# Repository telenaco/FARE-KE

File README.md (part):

# FARE-KE: Framework for Affordable, Reliable Kinesthetic Evaluation

## Overview

<p align="center"><span style="font-size: smaller;"><em>Figure 1: Exploded isometric view of the 6- and 3-axis load cell array assembly, showing the modular sensor housing units.</em></span></p>

FARE-KE is a comprehensive, standardized framework developed to address the growing need for accessible characterization methods for kinesthetic haptic devices. Born out of the challenges faced during the COVID-19 pandemic when laboratory access was limited, this framework provides researchers with the tools and methodologies to conduct precise haptic device evaluation using affordable components and open-source technologies.

The framework emerged from research on haptic device design and was refined through applications in three distinct case studies (VR Recoil, ProxyTouch, and HapticWhirl). FARE-KE aims to democratize haptic research by making characterization methods and tools accessible to researchers of all experience levels.

## Repository Structure

```
FARE-KE
├── Board_Evaluation
│   ├── ADC_Performance            # ADC testing and benchmarking studies
│   │   ├── adc_excitation_voltage_analysis  # Comparison of voltage stability
│   │   ├── adc_noise_variation_analysis     # Noise analysis at different OSR settings
│   │   └── adc_sampling_rate_analysis       # Evaluation of sampling performance
│   ├── Calibration_Methods        # Calibration methodologies for different load cells
│   │   ├── six_axis_calibration            # Matrix-based calibration approaches
│   │   └── three_axis_calibration          # Calibration for 3-axis sensors
│   └── Load_Cell_Comparison       # Comparative studies of load cell performance
│       ├── beam_load_cell_calibration      # Linear vs polynomial calibration
│       ├── beam_load_cell_comparison       # Temperature and drift analysis
│       └── hx711_vs_mcp3564_comparison     # Comparison of ADC performance
├── Haptic_Device_Testing
│   ├── Ramp_Response              # Implementation of ramp response analysis
│   │   ├── rampResponseAnalysis.py        # Analysis script for ramp data
│   │   └── rampResponseTelemetry.cpp      # Arduino code for ramp testing
│   └── Step_Response              # Implementation of step response analysis
│       ├── StepResponseAnalysis.py        # Analysis script for step data
│       └── stepResponseTelemetry.cpp      # Arduino code for step testing
├── MCP356x_Arduino_Library        # Core software components of FARE-KE
│   ├── lib/mcp356x                # Library for MCP356x ADCs
│   │   ├── examples               # Example implementations
│   │   │   ├── Basic              # Fundamental operations (reading, sampling)
│   │   │   ├── Calibration        # Calibration examples for different scenarios
│   │   │   ├── Comparison         # Comparison with other ADC technologies
│   │   │   ├── Filtering          # Signal filtering implementations
│   │   │   ├── LoadCells          # Multi-axis load cell configurations
│   │   │   └── Telemetry          # Data visualization and transmission
│   │   └── src                    # Core library source files
│   │       ├── MCP356x.cpp/h              # Base ADC interface
│   │       ├── MCP356x3axis.cpp/h         # 3-axis load cell support
│   │       ├── MCP356x6axis.cpp/h         # 6-axis force/torque plate
│   │       └── MCP356xScale.cpp/h         # Multi-load cell management
│   └── src                        # Main application code
├── MCP356x_DAQ_PCB_Board          # Hardware design for data acquisition
│   └── ffpcbBoard                 # Custom PCB for 12-channel data acquisition
│       ├── manufacturingPCB               # Gerber files for fabrication
│       └── PCB design files               # Schematics and BOM information
└── STL files and 3D models        # Physical components for framework implementation
    ├── 3-axis load cell STLs             # 3D printable parts for custom 3-axis sensors
    ├── 6-axis force plate STLs           # Components for force/torque plate assembly
    └── testbed designs                   # Mounting systems for various device types
```

## The FARE-KE Framework Architecture

FARE-KE consists of four integrated components to provide comprehensive haptic device characterization:

### 1. Hardware Framework

<p align="center"><span style="font-size: smaller;"><em>Figure 2: Complete 6-axis force/torque plate with ADC board and wiring, showing the integrated system.</em></span></p>

**Key Components:**
- **Load Cells**: Single-axis beam load cells, custom 3-axis, and 6-axis configurations
- **Data Acquisition System**: Custom PCB design integrating 3 x MCP3564 ADCs for 12-channel capture
- **Testbeds**: Modular aluminum designs for mounting kinesthetic devices and sensors

**Testbed Designs:**
The framework recommends using extruded aluminum (40×40mm) for testbed construction due to:
- Standardization and wide availability
- Excellent structural rigidity (minimal vibrations)
- Abundant accessories for mounting and adaptation
- Easy reconfiguration for different device sizes

The testbeds must be designed to emulate the device's operational context and accommodate the same quantity and configuration of actuators as the final prototype to ensure representative data capture.

The framework supports five types of kinesthetic feedback modalities:

1. **Direct Single-Axis Force**: For devices applying linear force directly to the user
2. **Single-Axis Impact**: For devices generating sudden bursts of energy
3. **In-line Forces**: For cable-driven exoskeletons and similar devices
4. **Rotational Joint Torque**: For devices generating torque around a pivot point
5. **Multi-axis Force/Torque**: For complex haptic controllers with multiple degrees of freedom

### 2. Data Acquisition Framework

**Components:**
- **MCP3564 ADCs**: 24-bit sigma-delta converters supporting up to 153.6 kSPS sampling
- **Op-amp Based Amplification**: Customizable gain to optimize ADC range utilization
- **Teensy 4.0 Integration**: High-speed processing of multiple ADC channels

<p align="center"><span style="font-size: smaller;"><em>Figure 4: Detailed assembly of the custom 12-channel Data Acquisition PCB, showing component layout and interconnections.</em></span></p>

<p align="center"><span style="font-size: smaller;"><em>Figure 5: PCB board design schematic, illustrating the intricate routing and component placement for the 12-channel ADC system.</em></span></p>

**Key Features:**
- **Sampling Rate**: Up to 10 kSPS on a single channel with internal clock
- **Resolution**: Effective resolution of 16+ bits due to signal conditioning and oversampling
- **Channels**: Support for 12 simultaneous channels when using three ADCs

**Excitation Voltage Comparison:**
| Parameter          | HX711 ADC (V) | MCP3564 ADC (V) |
|--------------------|---------------|-----------------|
| Mean voltage       | 4.2913        | 3.2840          |
| Standard deviation | 0.0140        | 0.0133          |
| Range (Max - Min)  | 0.3119        | 0.2533          |

Both ADC circuits exhibit similar interference levels in the frequency domain. The MCP3564 showed a slightly smaller standard deviation.

### 3. Calibration Framework

**Calibration Approaches:**
- **Single-Axis Calibration**: Polynomial regression providing up to 0.9999 R² fit
- **3-Axis Calibration**: Multi-point calibration with matrix-based crosstalk compensation
- **6-Axis Calibration**: Least-squares optimization for complex force/torque interactions

<p align="center"><span style="font-size: smaller;"><em>Figure 6: Comparative analysis of different calibration techniques for beam load cells, demonstrating the linearity and accuracy of polynomial regression, linear regression, and scaling factor methods.</em></span></p>

**Calibration Mathematics:**

For single-axis load cells, three calibration approaches are evaluated:
1. **Scaling Factor**: `y = Kx` where K is a constant factor
2. **Linear Regression**: `y = mx + b` where m is slope and b is intercept
3. **Polynomial Regression**: `y = ax² + bx + c` for nonlinear behavior

For 3-axis load cells, the calibration matrix (K) accounts for both sensitivity and crosstalk:
```
[Fx]   [K11 K12 K13] [Rx]
[Fy] = [K21 K22 K23] [Ry]
[Fz]   [K31 K32 K33] [Rz]
```
Where Fx, Fy, Fz are forces, and Rx, Ry, Rz are sensor readings.

For the 6-axis force/torque plate, the 12 individual load cell readings are combined to calculate forces and torques:
```
Fx = LCAxf + LCBxf + LCCxf + LCDxf
Fy = LCAyf + LCByf + LCCyf + LCDyf
Fz = LCAzf + LCBzf + LCCzf + LCDzf
Mx = (plateLength/2) * (LCAzf + LCBzf - LCCzf - LCDzf)
My = (plateWidth/2) * (-LCAzf + LCBzf + LCCzf - LCDzf)
Mz = (plateWidth/2) * (LCAyf - LCByf + LCCyf - LCDyf) + 
     (plateLength/2) * (LCAxf + LCBxf - LCCxf - LCDxf)
```
Where LC[A-D][x-z]f represents force readings from each load cell in each direction.

### 4. Analysis Framework

**Performance Metrics:**
- **Physical Properties**: 7 metrics describing basic device characteristics
- **Ramp Analysis**: 7 metrics capturing force capabilities and static behavior
- **Step Response Analysis**: 5 metrics describing dynamic performance

## Hardware Components

### Data Acquisition System

The core of the FARE-KE framework is a custom 12-channel DAQ board built around the MCP3564 24-bit ADC:

- **Channels:** 12 differential input channels (3 MCP3564 ADCs × 4 channels each)
- **Resolution:** 24-bit per channel
- **Sampling Rate:** Up to 11.59 kSPS per channel with OSR=32
- **Multiple Configurations:** Adjustable oversampling ratio (OSR) to balance between noise rejection and sampling speed
- **Amplification:** Integrated amplification stage with MCP6V97 op-amps
- **Power Supply:** 5-12V input with separate analog and digital power domains
- **Power Consumption:** ~76.4mA with all 12 channels active

The PCB design files are available in the `MCP356x_DAQ_PCB_Board/ffpcbBoard/manufacturingPCB/` directory.

### Load Cell Configurations

#### 1. Single-Axis Beam Load Cells

The framework has validated the performance of three models:

- **TAL220:** 10kg capacity, demonstrated excellent linearity (R² > 0.999)
- **Degraw:** 5kg capacity, good performance with slightly higher noise
- **CZL635:** 5kg capacity, good performance with lower noise

| Load Cell | Capacity (kg) | Slope (counts/gf) | R² Value | Sensitivity (mgf) | Peak-to-peak noise (gf) |
|-----------|---------------|-------------------|----------|-------------------|--------------------------|
| TAL220    | 10            | 1787.65           | 0.99998  | 0.56              | 17.105                   |
| Degraw    | 5             | 2517.44           | 0.99995  | 0.40              | 10.152                   |
| CZL635    | 5             | 3033.73           | 0.99997  | 0.33              | 9.784                    |

**Temperature Drift Analysis:**
All three load cells showed sensitivity to temperature fluctuations, but with different characteristics:
- **TAL220:** Strong positive linear correlation with temperature (Pearson: 0.93, Spearman: 0.97)
- **Degraw:** Strong negative linear correlation (Pearson: -0.78, Spearman: -0.93)
- **CZL635:** Moderate positive correlation (Pearson: 0.54) but weaker monotonic relationship (Spearman: 0.12)

The maximum observed deviation was approximately 10gf over a 24-hour period (0.435% of the reading).

#### 2. Button & S-Type Load Cells

For specific applications requiring in-line force measurement:

| Load Cell Model         | Max capacity | Cost  | Type                  | Dimensions (mm)   |
|-------------------------|--------------|-------|-----------------------|-------------------|
| Honeywell FSS015WNSB    | 1.5kg        | ~70€  | Compression Load Cell | 9.14x3.18x5.59    |
| Phidget Button Load Cell| 50kg         | ~45€  | Compression Load Cell | 9mm height 25mm ⌀ |
| Phidget Button Load Cell| 200kg        | ~45€  | Compression Load Cell | 9mm height 25mm ⌀ |
| DYLY-106 (S-type)       | 10kg         | ~50€  | S-Type Load Cell      | 25x30x12mm        |

These offer advantages for inline force measurements but typically cost more due to complex manufacturing.

#### 3. 3-Axis Load Cell

Custom-designed assemblies using three single-axis beam load cells arranged orthogonally:

- 3D-printed components ensure proper alignment
- Calibration matrices compensate for crosstalk between axes
- Validated using polynomial regression calibration methods

<p align="center"><span style="font-size: smaller;"><em>Figure 3: Side view of a 3-axis load cell mounted on the force/torque plate, showing mounting method.</em></span></p>

| Calibration Method | MAE (g) | RMSE (g) | Max Error (g) |
|--------------------|---------|----------|---------------|
| Single-Point       | 8.91    | 15.24    | 70.43         |
| Least Squares      | 8.70    | 14.72    | 67.29         |
| Polynomial Regression | 7.54 | 11.28    | 44.93         |

**Assembly Process:**
1. Apply aluminum epoxy to the load cell holders
2. Mount load cells using 3D-printed parts (base, elbows, center piece)
3. Mark and drill 2.5mm holes through the load cells
4. Tap the holes to create 3mm threads
5. Secure joints using M3 screws

#### 4. 6-Axis Force/Torque Plate

Comprehensive solution for measuring forces and torques in all directions:

- Four 3-axis load cells arranged between two acrylic plates (12mm thick)
- 12 total channels measuring force components
- Mathematical algorithms combine readings to calculate 3 forces and 3 torques
- Multipoint calibration procedures compensate for crosstalk and nonlinear behavior

| Metric    | Raw Readings | Calibrated |
|-----------|--------------|-------------|
| MAPE (%)  | 2.814737     | 1.849263    |
| R-squared | 0.983804     | 0.999691    |

**Crosstalk Reduction:**
The calibration matrix substantially reduced crosstalk, particularly along the torque axes:

| Axis | Pre-calibration Std Dev | Post-calibration Std Dev | Improvement Factor |
|------|------------------------|--------------------------|-------------------|
| Fx   | 0.1139                 | 0.0224                   | ~5x               |
| Fy   | 0.0821                 | 0.0377                   | ~2x               |
| Fz   | 0.3907                 | 0.0343                   | ~11x              |
| Mx   | 0.0846                 | 0.0154                   | ~5.5x             |
| My   | 0.0979                 | 0.0085                   | ~11.5x            |
| Mz   | 0.0528                 | 0.0043                   | ~12x              |

### Microcontroller

The framework is designed to work with Teensy 4.0 microcontrollers:

- 600 MHz ARM Cortex-M7 processor
- Support for high-speed SPI communication (up to 20 MHz)
- USB connectivity for data logging and visualization
- Sufficient I/O pins for multiple ADC control

## Software Components

### Core Library Structure

The `MCP356x_Arduino_Library` implements a hierarchical class structure:

- **MCP356x:** Base class for interfacing with the MCP3564 ADC
- **MCP356xScale:** Mid-level class for managing single-axis load cells
- **MCP356x3axis:** Class for 3-axis load cell measurement and calibration
- **MCP356x6axis:** High-level class for the complete force/torque plate

### Calibration Utilities

Located in `Board_Evaluation/Calibration_Methods/`, these tools provide:

- Single-axis load cell calibration using polynomial regression
- 3-axis load cell calibration with crosstalk compensation
- 6-axis force/torque plate multipoint calibration
- Validation scripts to verify calibration accuracy

### Analysis Scripts

The `Haptic_Device_Testing/` directory contains scripts for standardized performance evaluation:

- **Ramp Response Analysis:** `rampResponseTelemetry.cpp` and `rampResponseAnalysis.py`
- **Step Response Analysis:** `stepResponseTelemetry.cpp` and `StepResponseAnalysis.py`

### Data Logging Tools

Two primary tools are supported for data acquisition and visualization:

**TyCommander:**
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
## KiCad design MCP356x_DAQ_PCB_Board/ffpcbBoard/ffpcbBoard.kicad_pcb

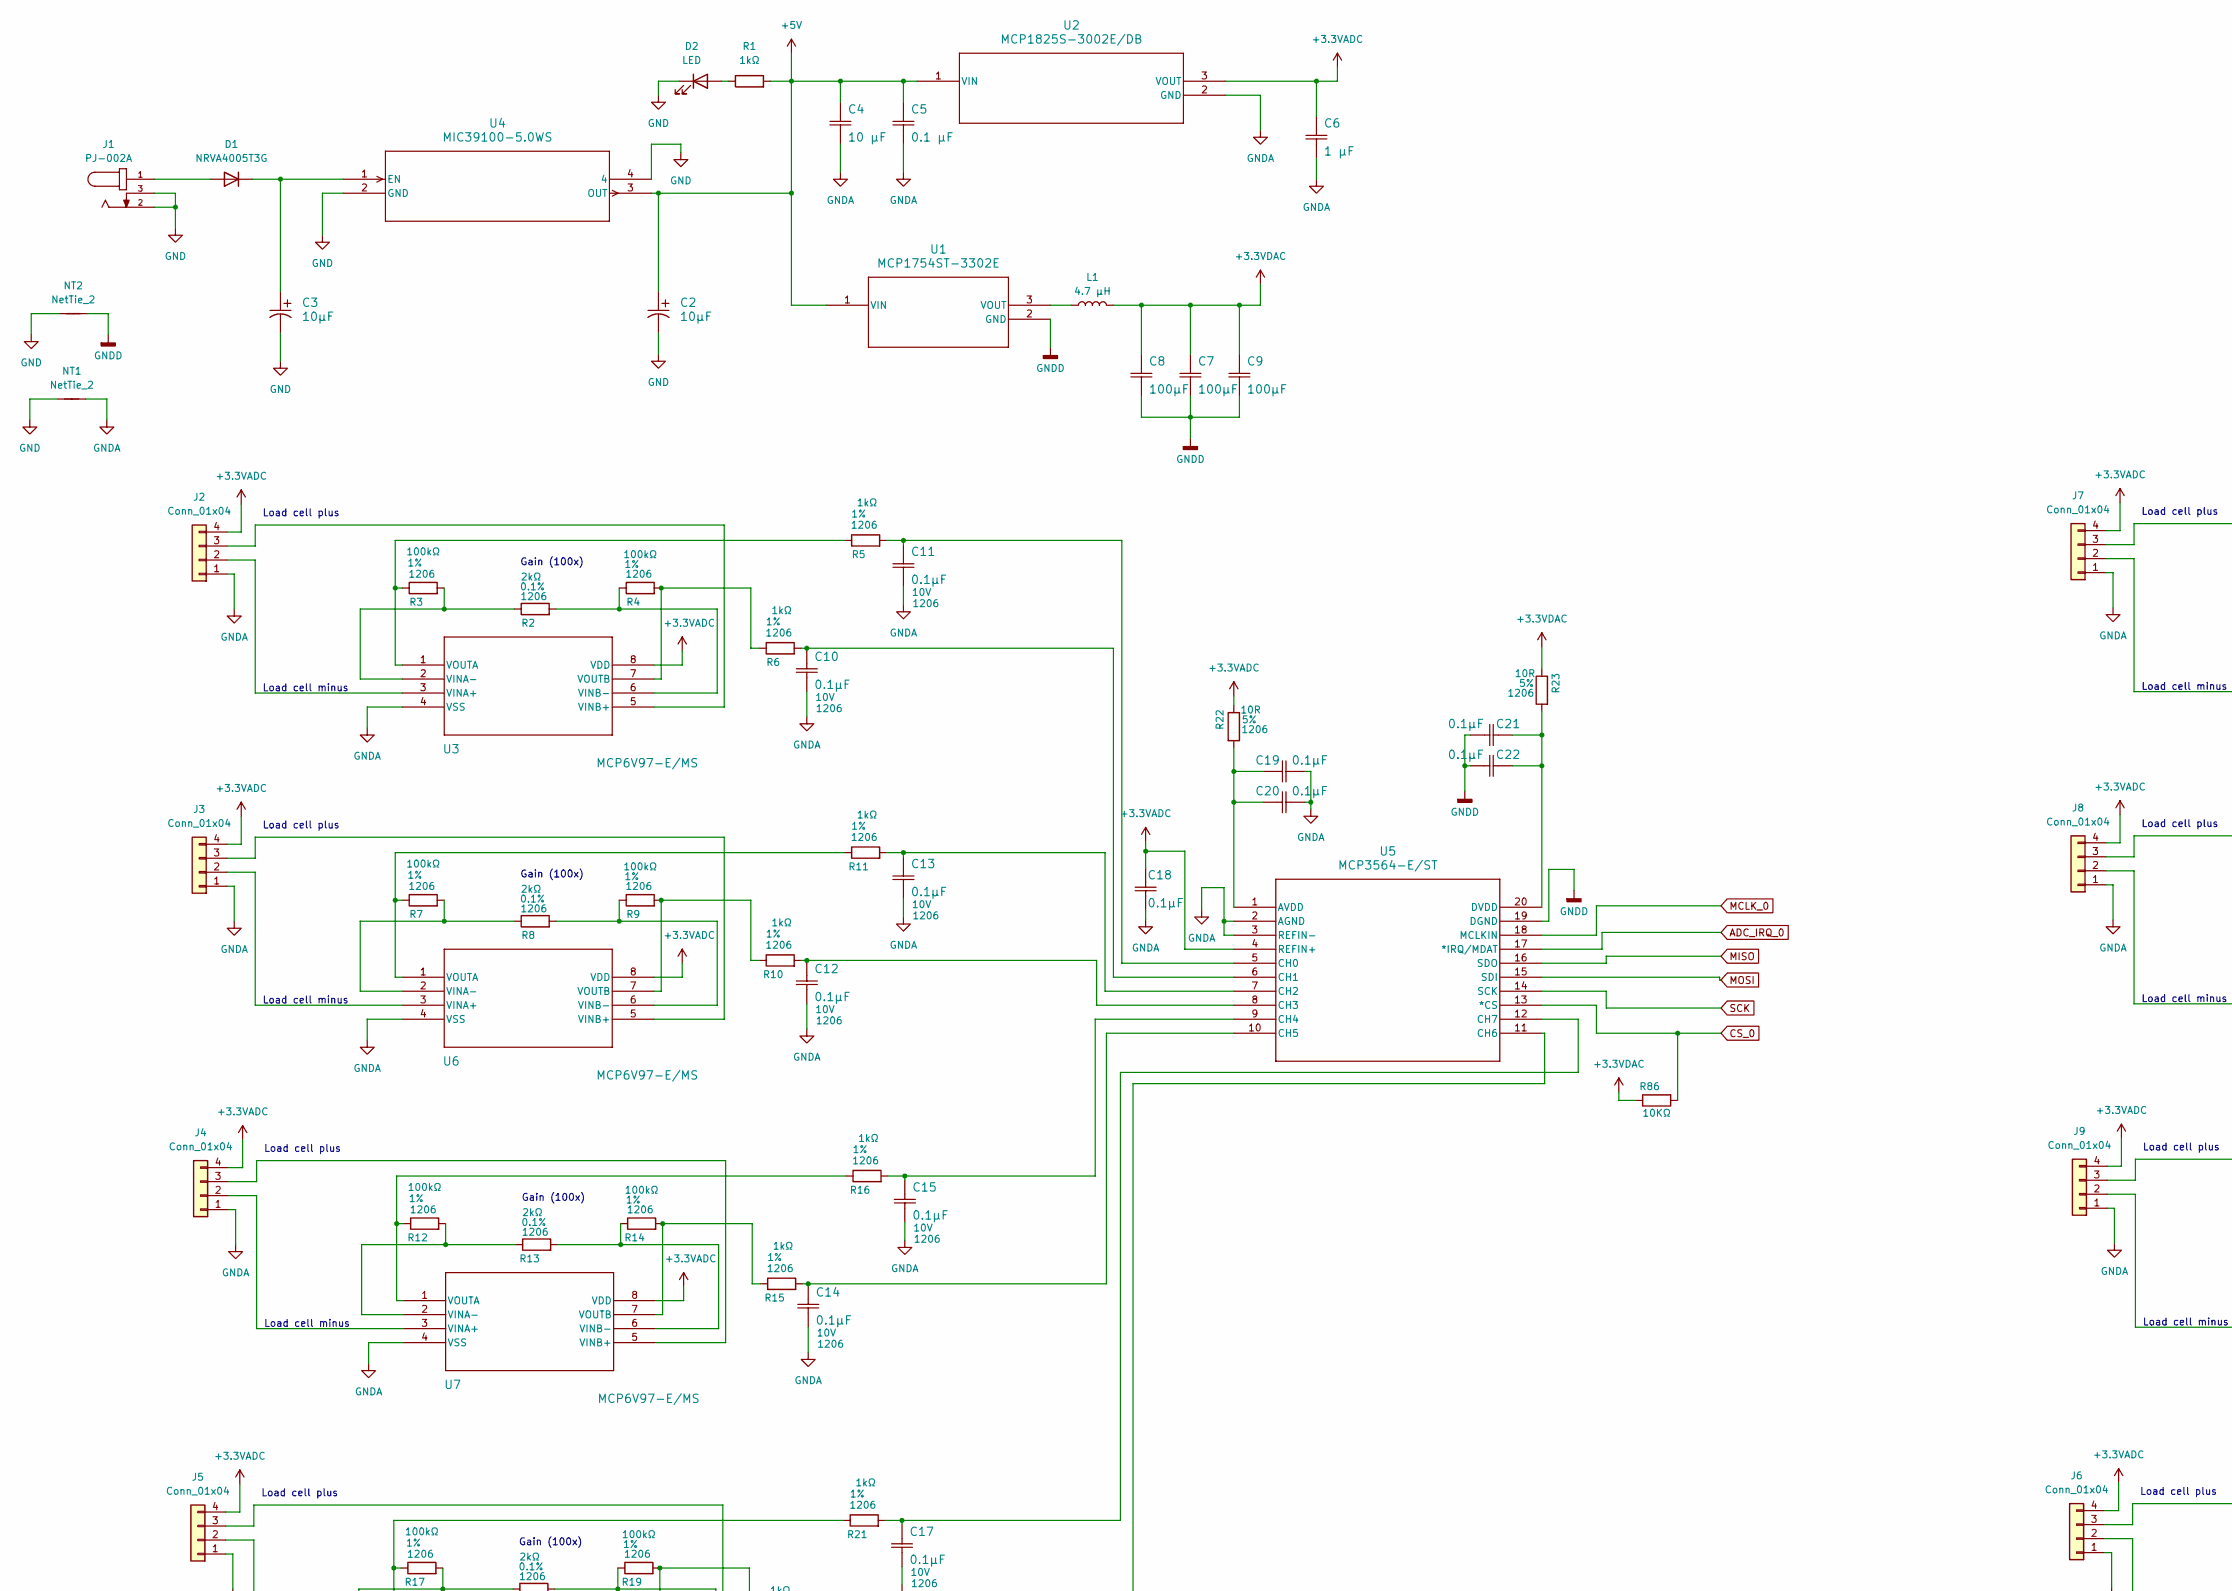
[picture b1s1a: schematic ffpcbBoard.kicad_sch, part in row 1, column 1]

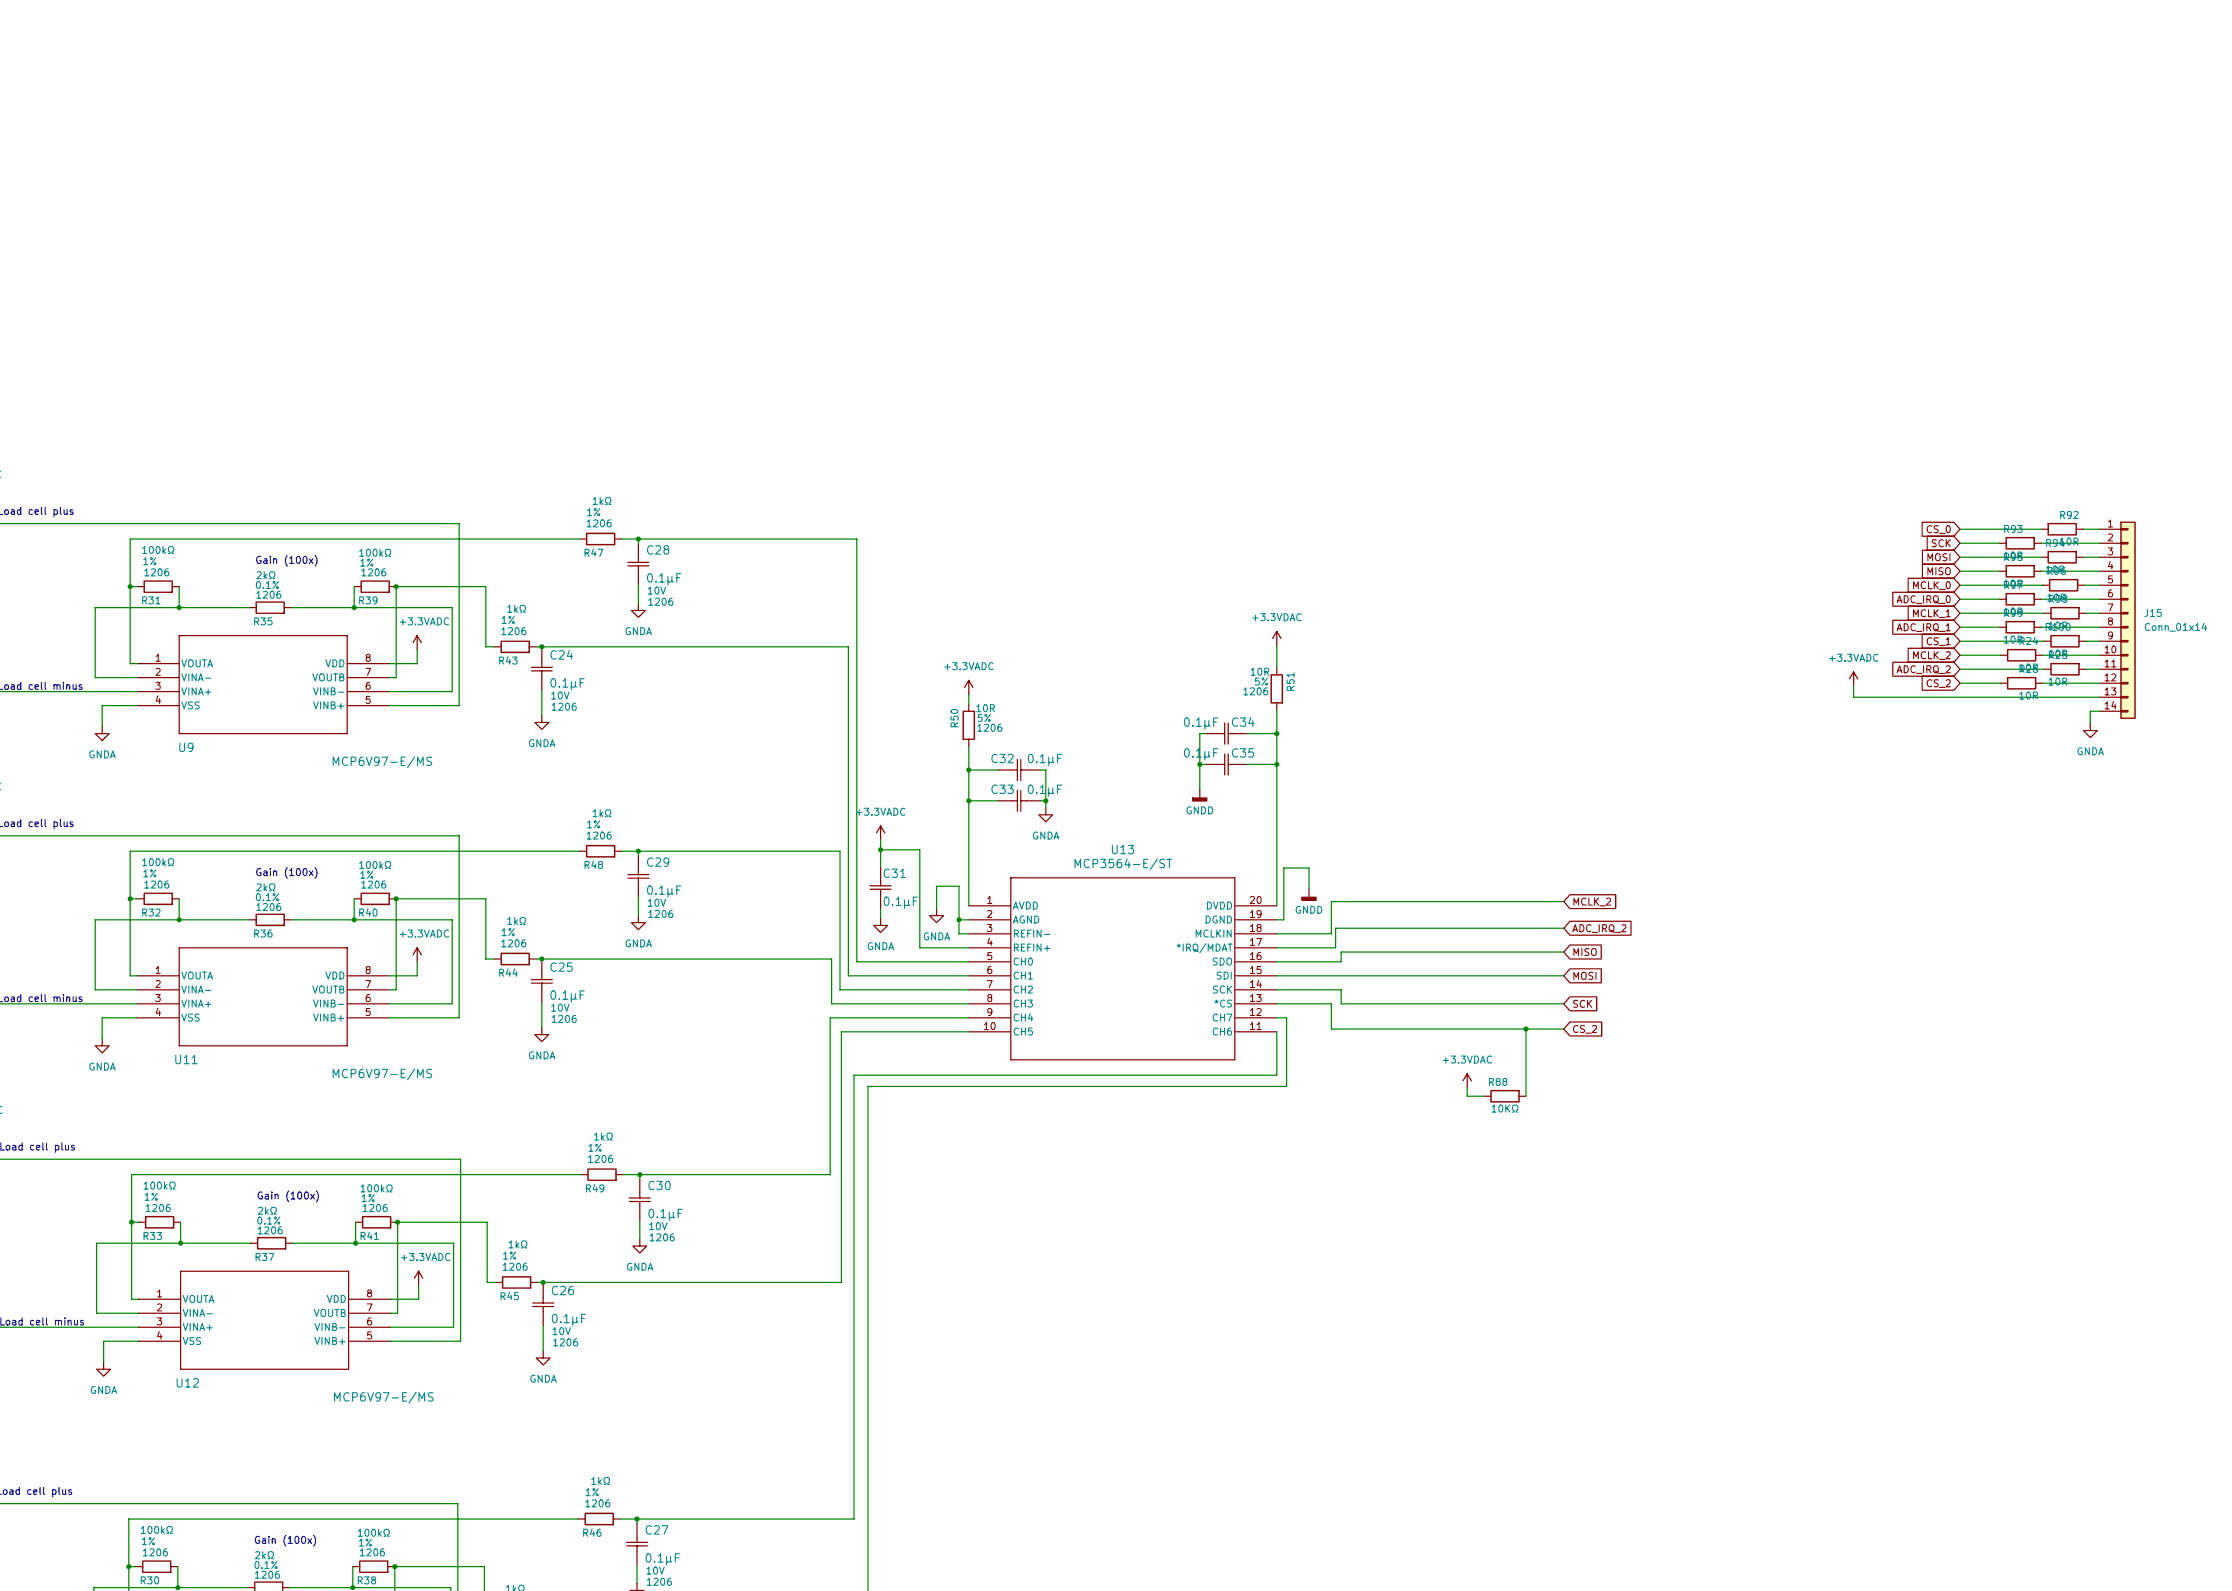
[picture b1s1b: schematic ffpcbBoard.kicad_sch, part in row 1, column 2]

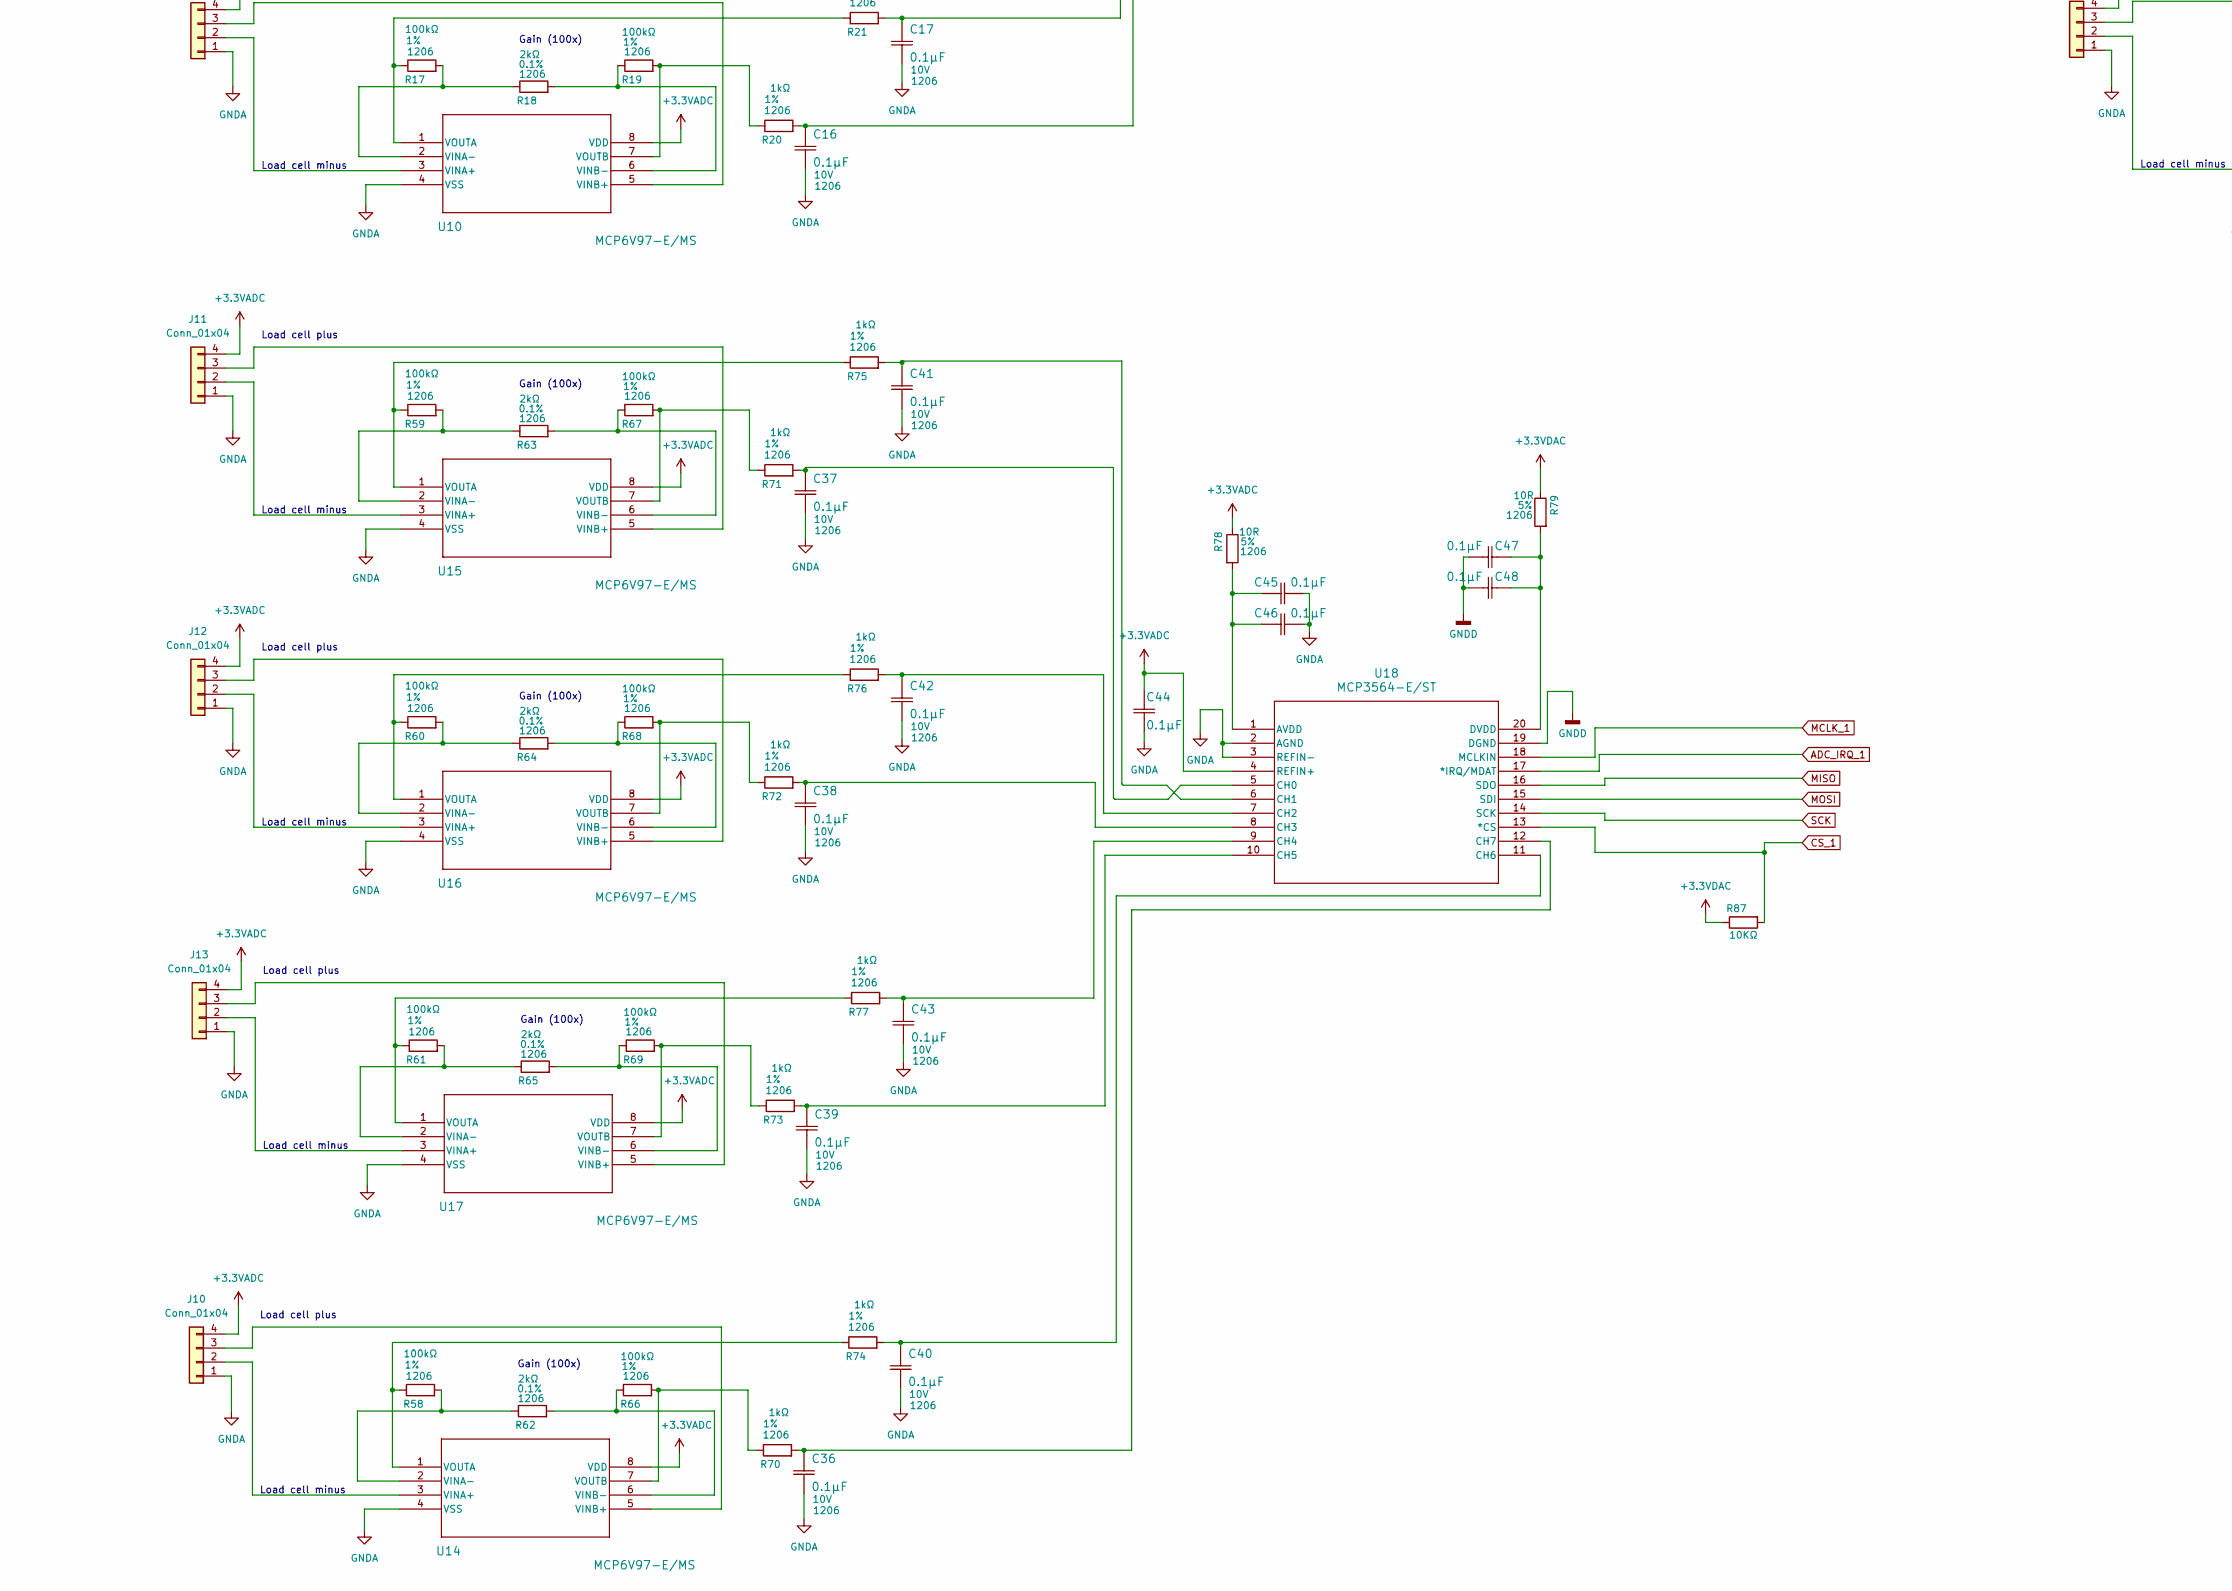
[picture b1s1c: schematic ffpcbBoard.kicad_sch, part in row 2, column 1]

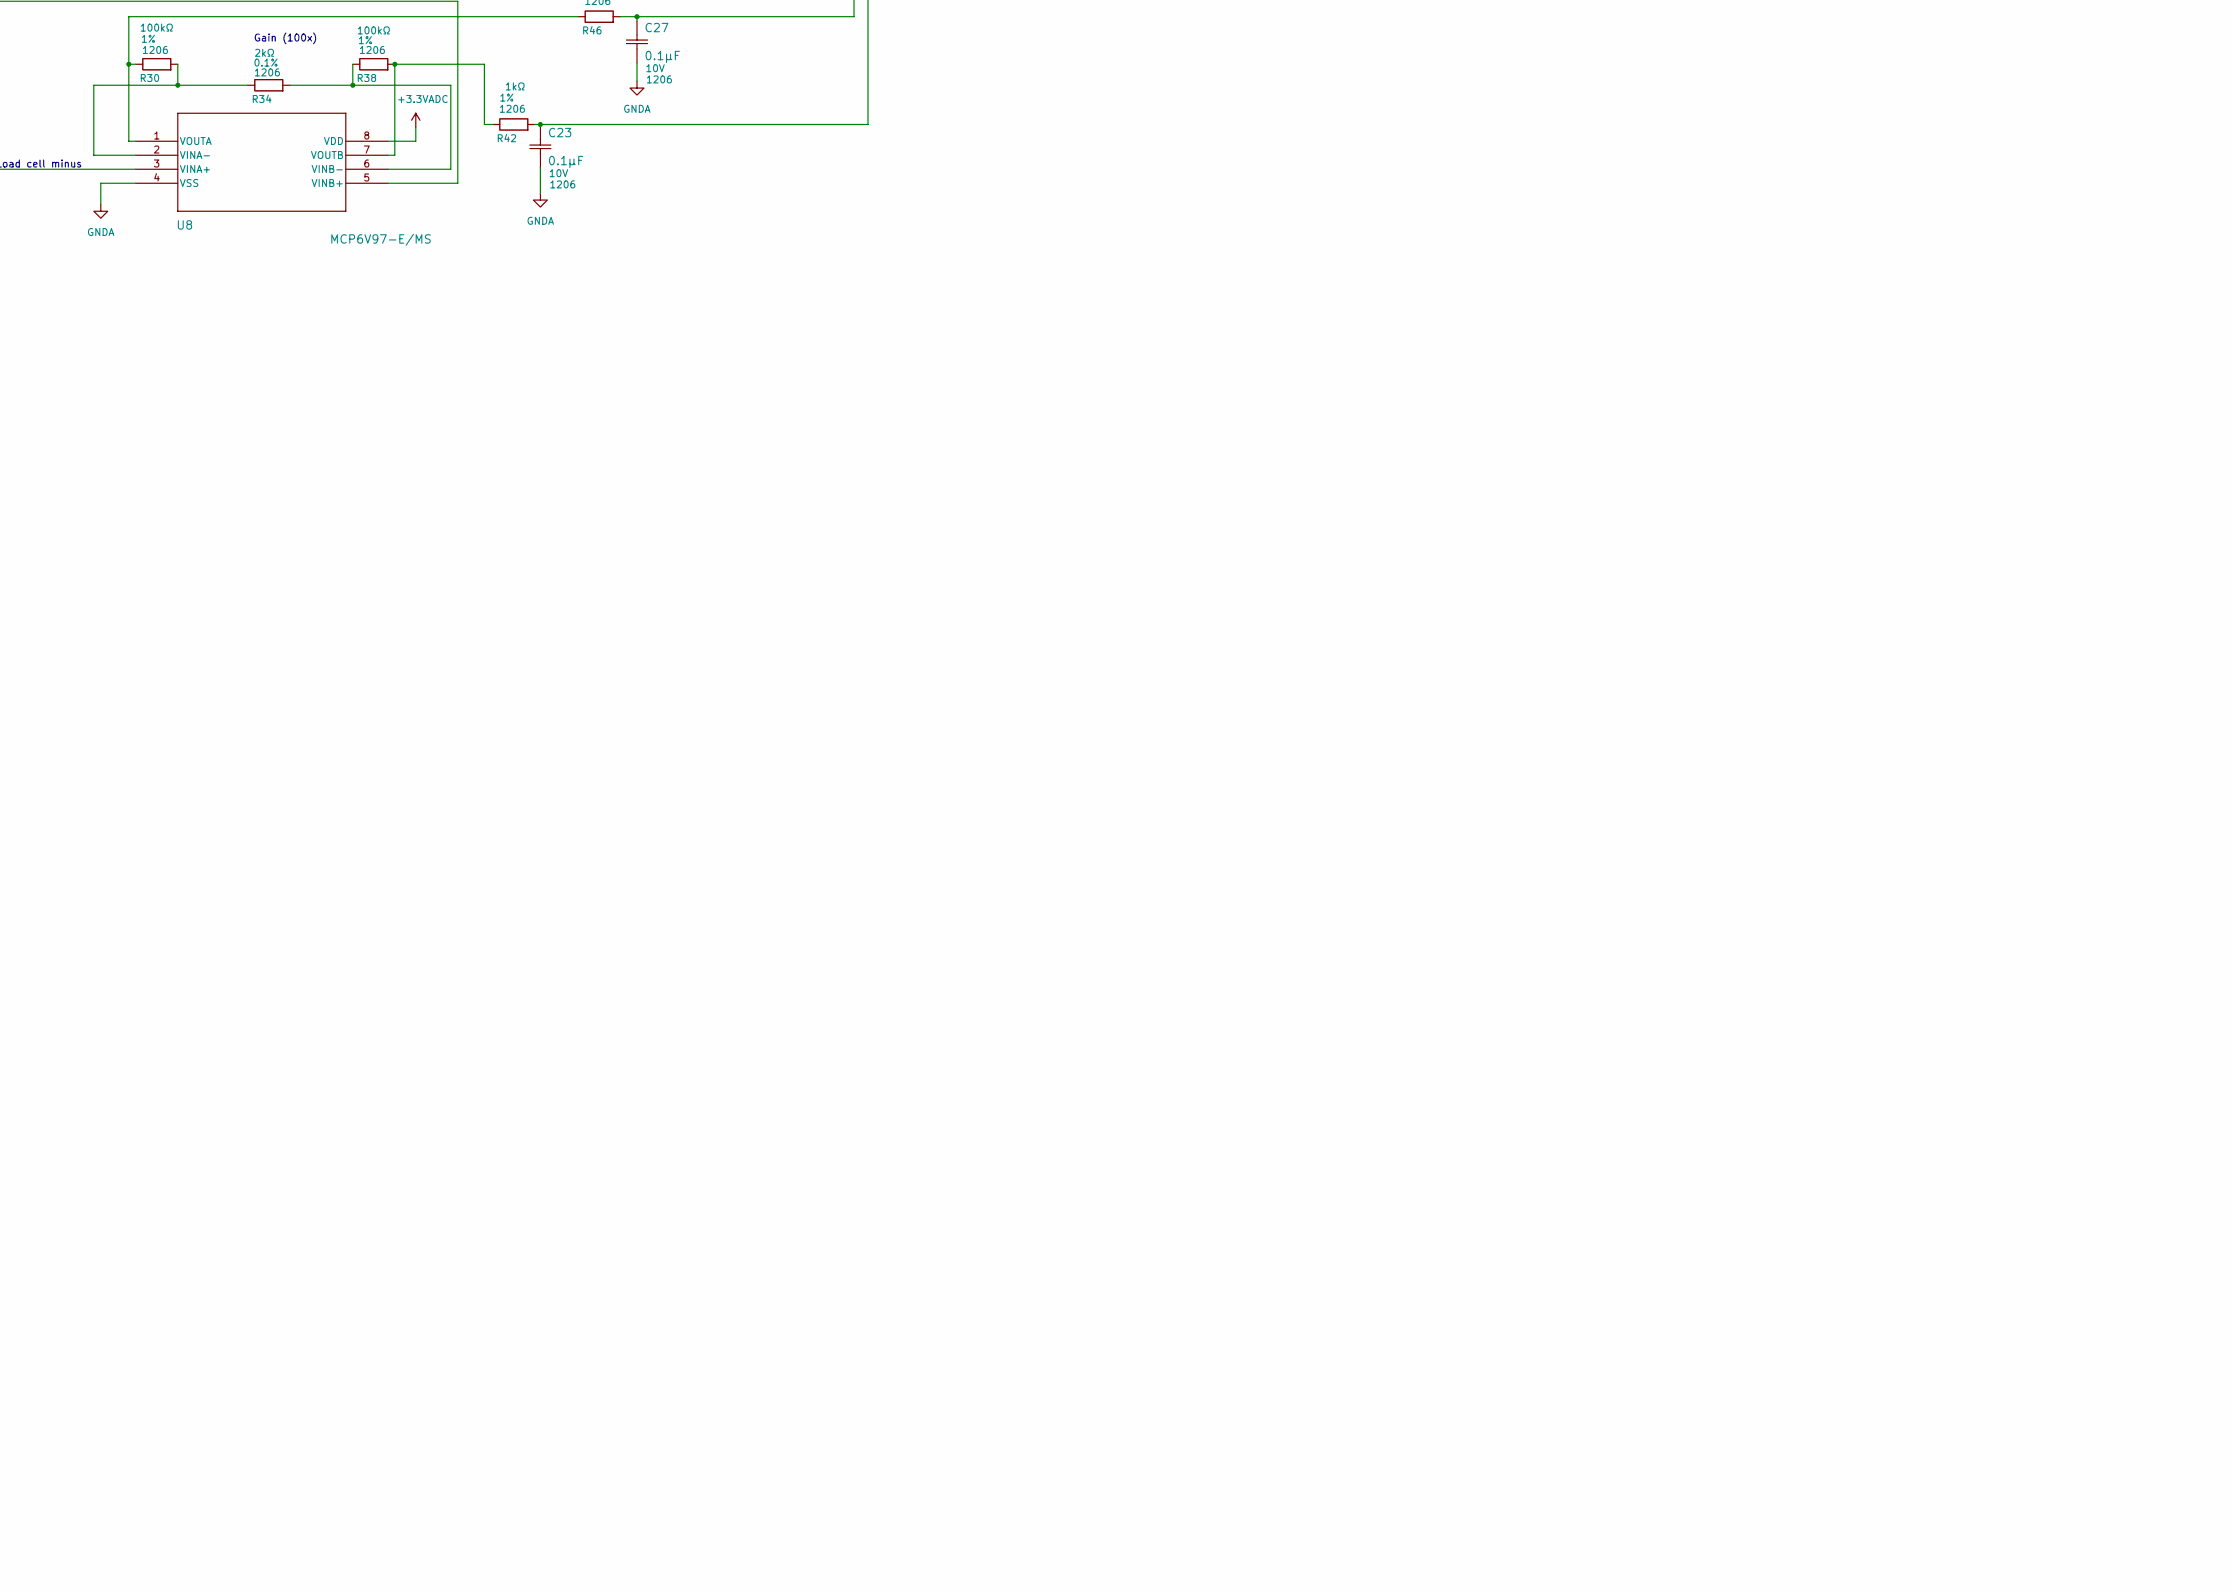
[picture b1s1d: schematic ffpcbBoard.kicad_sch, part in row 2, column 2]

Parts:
C2, C3: 10µF; TAJB_AVX-M
C4: 10 µF; CAPC340180_180N_KEM-M
C5: 0.1 µF; CAPC340180_180N_KEM-M
C6: 1 µF; CAPC340180_180N_KEM-M
C7, C8, C9: 100µF; CAPC340180_180N_KEM-M
C10, C11, C12, C13, C14, C15, C16, C17, C18, C19, C20, C21, C22, C23, C24, C25, C26, C27, C28, C29, C30, C31, C32, C33, C34, C35, C36, C37, C38, C39, C40, C41, C42, C43, C44, C45, C46, C47, C48: 0.1µF; CAPC340180_180N_KEM-M
D1: NRVA4005T3G; D_SMA
D2: LED; LED_1206_3216Metric
J1: PJ-002A; CUI_PJ-002A
J2, J3, J4, J5, J6, J7, J8, J9, J10, J11, J12, J13: Conn_01x04; FanPinHeader_1x04_P2.54mm_Vertical
J15: Conn_01x14; PinSocket_1x14_P2.54mm_Vertical
L1: 4.7 µH; L_1206_3216Metric_Pad1.22x1.90mm_HandSolder
NT1, NT2: NetTie_2; NetTie-2_SMD_Pad0.5mm
R1, R5, R6, R10, R11, R15, R16, R20, R21, R42, R43, R44, R45, R46, R47, R48, R49, R70, R71, R72, R73, R74, R75, R76, R77: 1kΩ; R_1206_3216Metric_Pad1.30x1.75mm_HandSolder
R2, R8, R13, R18, R34, R35, R36, R37, R62, R63, R64, R65: 2kΩ; R_1206_3216Metric_Pad1.30x1.75mm_HandSolder
R3, R4, R7, R9, R12, R14, R17, R19, R30, R31, R32, R33, R38, R39, R40, R41, R58, R59, R60, R61, R66, R67, R68, R69: 100kΩ; R_1206_3216Metric_Pad1.30x1.75mm_HandSolder
R22, R23, R24, R25, R26, R50, R51, R78, R79, R92, R93, R94, R95, R96, R97, R98, R99, R100: 10R; R_1206_3216Metric_Pad1.30x1.75mm_HandSolder
R86, R87, R88: 10KΩ; R_1206_3216Metric_Pad1.30x1.75mm_HandSolder
U1: MCP1754ST-3302E; SOT-223_3MC_MCH-M
U2: MCP1825S-3002E/DB; SOT-223_3MC_MCH-M
U3, U6, U7, U8, U9, U10, U11, U12, U14, U15, U16, U17: MCP6V97-E/MS; MSOP8_MS_MCH-M
U4: MIC39100-5.0WS; SOT-223_S_MCL-M
U5, U13, U18: MCP3564-E/ST; TSSOP20_ST_MCH-M

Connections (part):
+3.3VADC: C6.1, C18.1, C31.1, C44.1, J2.4, J3.4, J4.4, J5.4, J6.4, J7.4, J8.4, J9.4, J10.4, J11.4, J12.4, J13.4, J15.13, R22.1, R50.1, R78.1, U2.3 (VOUT), U3.8 (VDD), U5.4 (REFIN+), U6.8 (VDD), U7.8 (VDD), U8.8 (VDD), U9.8 (VDD), U10.8 (VDD), U11.8 (VDD), U12.8 (VDD), U13.4 (REFIN+), U14.8 (VDD), U15.8 (VDD), U16.8 (VDD), U17.8 (VDD), U18.4 (REFIN+)
+3.3VDAC: C7.1, C8.1, C9.1, L1.2, R23.1, R51.1, R79.1, R86.1, R87.1, R88.1
+5V: C2.1, C4.1, C5.1, R1.2, U1.1 (VIN), U2.1 (VIN), U4.3 (OUT)
ADC_IRQ_0: R97.1, U5.17 (*IRQ/MDAT)
ADC_IRQ_1: R99.1, U18.17 (*IRQ/MDAT)
ADC_IRQ_2: R25.1, U13.17 (*IRQ/MDAT)
CS_0: R86.2, R92.2, U5.13 (*CS)
CS_1: R87.2, R100.1, U18.13 (*CS)
CS_2: R26.2, R88.2, U13.13 (*CS)
GND: C2.2, C3.2, D2.1 (K), J1.2, J1.3, NT1.1, NT2.1, U4.2 (GND), U4.4
GNDA: C4.2, C5.2, C6.2, C10.2, C11.2, C12.2, C13.2, C14.2, C15.2, C16.2, C17.2, C18.2, C19.2, C20.2, C23.2, C24.2, C25.2, C26.2, C27.2, C28.2, C29.2, C30.2, C31.2, C32.2, C33.2, C36.2, C37.2, C38.2, C39.2, C40.2, C41.2, C42.2, C43.2, C44.2, C45.2, C46.2, J2.1, J3.1, J4.1, J5.1, J6.1, J7.1, J8.1, J9.1, J10.1, J11.1, J12.1, J13.1, J15.14, NT1.2, U2.2 (GND), U3.4 (VSS), U5.2 (AGND), U5.3 (REFIN-), U6.4 (VSS), U7.4 (VSS), U8.4 (VSS), U9.4 (VSS), U10.4 (VSS), U11.4 (VSS), U12.4 (VSS), U13.2 (AGND), U13.3 (REFIN-), U14.4 (VSS), U15.4 (VSS), U16.4 (VSS), U17.4 (VSS), U18.2 (AGND), U18.3 (REFIN-)
GNDD: C7.2, C8.2, C9.2, C21.2, C22.2, C34.2, C35.2, C47.2, C48.2, NT2.2, U1.2 (GND), U5.19 (DGND), U13.19 (DGND), U18.19 (DGND)
MCLK_0: R96.1, U5.18 (MCLKIN)
MCLK_1: R98.1, U18.18 (MCLKIN)
MCLK_2: R24.2, U13.18 (MCLKIN)
MISO: R95.1, U5.16 (SDO), U13.16 (SDO), U18.16 (SDO)
MOSI: R94.1, U5.15 (SDI), U13.15 (SDI), U18.15 (SDI)
unnamed: D1.2 (A), J1.1
unnamed: C3.1, D1.1 (K), U4.1 (EN)
unnamed: D2.2 (A), R1.1
unnamed: J2.2, U3.3 (VINA+)
unnamed: J2.3, U3.5 (VINB+)
unnamed: J3.2, U6.3 (VINA+)
unnamed: J3.3, U6.5 (VINB+)
unnamed: J4.2, U7.3 (VINA+)
unnamed: J4.3, U7.5 (VINB+)
unnamed: J5.2, U10.3 (VINA+)
unnamed: J5.3, U10.5 (VINB+)
unnamed: J6.2, U8.3 (VINA+)
unnamed: J6.3, U8.5 (VINB+)
unnamed: J7.2, U9.3 (VINA+)
unnamed: J7.3, U9.5 (VINB+)
unnamed: J8.2, U11.3 (VINA+)
unnamed: J8.3, U11.5 (VINB+)
unnamed: J9.2, U12.3 (VINA+)
unnamed: J9.3, U12.5 (VINB+)
unnamed: J10.2, U14.3 (VINA+)
unnamed: J10.3, U14.5 (VINB+)
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
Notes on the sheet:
Load cell plus
Load cell minus
Gain (100x)

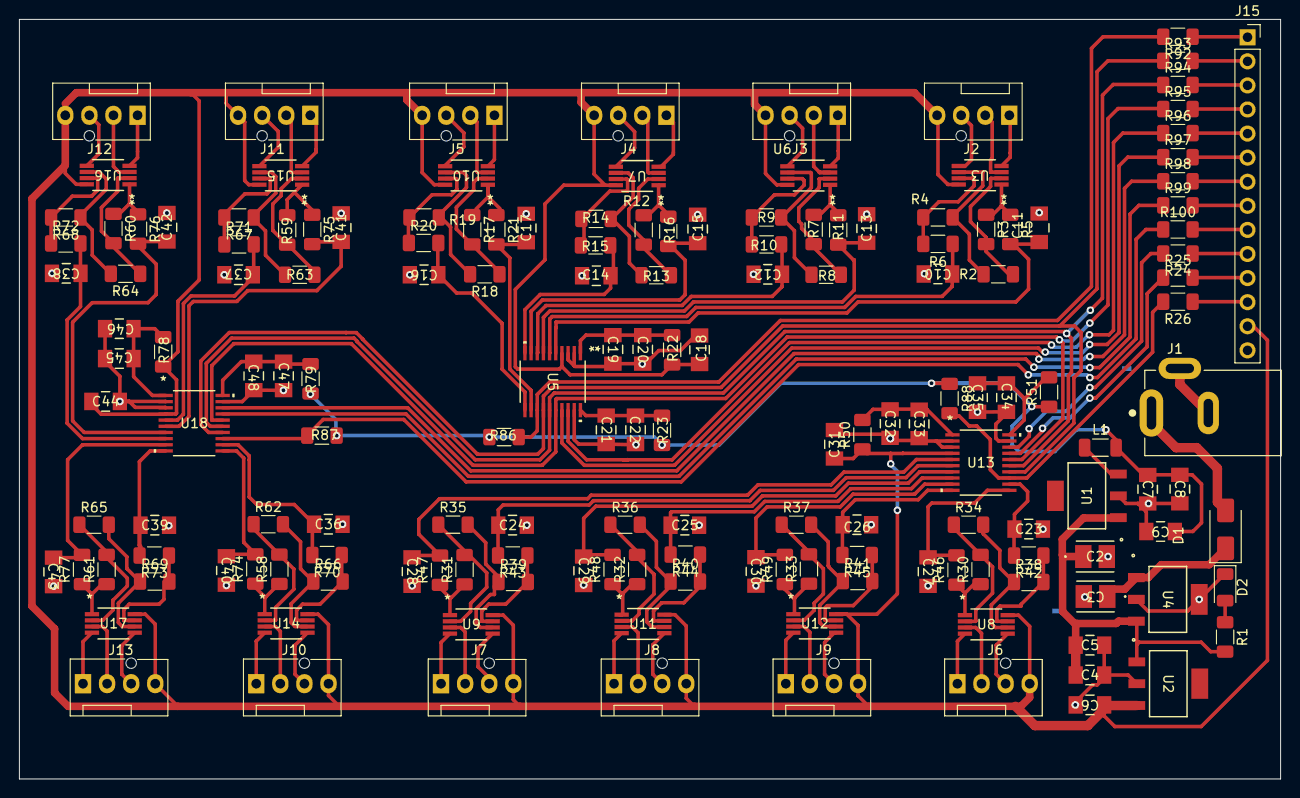
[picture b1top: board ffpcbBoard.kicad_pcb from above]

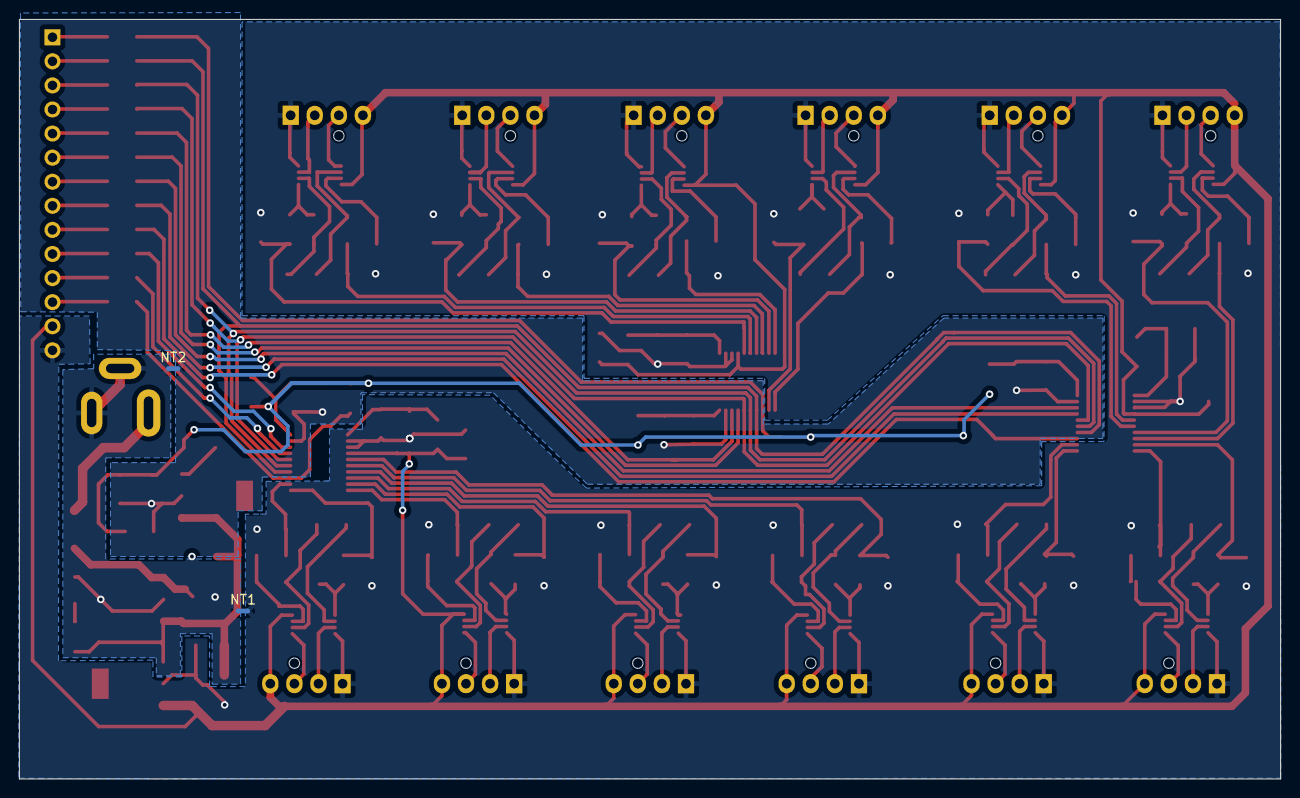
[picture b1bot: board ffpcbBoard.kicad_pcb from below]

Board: 2 copper layers, 133.0 x 80.1 mm, 166 parts (2 on the bottom side), 136 nets.

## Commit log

2024-04-01 init
2025-03-21 upload local files

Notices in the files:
README.md:
License:
This project is released under the MIT License. See the LICENSE file for details.
If you use FARE-KE in your research, please cite:
@thesis{bernamoya2025fare,
title={FARE-KE: Framework for Affordable, Reliable Kinesthetic Evaluation},
author={Berna Moya, Jose Luis},
year={2025},
school={University of Sussex}
License: MIT
